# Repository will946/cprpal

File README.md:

# CPRPal — Real-Time CPR Feedback and Training Device

---

## Table of Contents

- [Project Overview](#project-overview)
- [Repository Structure](#repository-structure)
- [System Architecture](#system-architecture)
- [Hardware Components](#hardware-components)
- [Wiring and Pin Assignments](#wiring-and-pin-assignments)
- [PCB Design](#pcb-design)
- [Firmware](#firmware)
- [Operating Modes](#operating-modes)
- [User Operation](#user-operation)
- [Signal Processing](#signal-processing)
- [Power System](#power-system)
- [Cloud and Web Application](#cloud-and-web-application)
- [Setup and Installation](#setup-and-installation)
- [Library Dependencies](#library-dependencies)

---

## Project Overview

CPRPal is a portable, puck-shaped CPR coaching device designed to help untrained bystanders and CPR trainees perform chest compressions with correct force, rhythm, and body positioning during a cardiac emergency or training session.

Sudden cardiac arrest is responsible for approximately 93% of out-of-hospital cardiac arrest deaths. Survival probability drops roughly 10% per minute without CPR or AED intervention, yet only about 3% of the U.S. population is CPR certified annually. CPRPal addresses this gap by providing real-time, easy-to-interpret feedback that requires no prior training to use.

The device is placed between the rescuer's hands and the patient's sternum during chest compressions. It measures compression force directly using a load cell, tracks body posture using a 9-DOF IMU, monitors for heartbeat presence using a PPG optical sensor, and delivers feedback through a color-coded NeoPixel LED ring, a 2.8" TFT LCD display, and a 100 BPM audio metronome buzzer.

**Emergency Mode** operates fully standalone with no Wi-Fi required, providing immediate real-time feedback the moment the button is pressed.

**Training Mode** connects to Wi-Fi, runs a 2-minute guided session, and uploads averaged session metrics to an Azure-hosted cloud dashboard for review.

The final prototype measures 4.5" x 4.5" x 2.25" and runs for over 15 hours on four AA batteries at a normal operating draw of approximately 155 mA.

CPRPal Demo: https://drive.google.com/file/d/1d1auYhc-_jhG4WK9BlywpUfyi4_rIxLO/view?usp=sharing
(Note video isn't perfectly sync with operation)

| Rendering | Final Build |
|---|---|
|  |  | 

---

## Repository Structure

```
CPRPal/
├── 3DModel/
│   └── Mechanical enclosure and CAD files
│       - Top shell with lattice structure and LCD/button/LED cutouts
│       - Bottom shell with battery pocket, support beams, and hard stops
│       - Full assembly files for PLA 3D printing
│
├── ArduinoCode/
│   └── CPRPal.ino — Main ESP32 firmware (FreeRTOS-based)
│       - Sensor integration (HX711, BNO055, PPG)
│       - Real-time signal processing and CPM detection
│       - LED and display feedback systems
│       - Emergency and Training mode logic
│       - Power management and idle sleep
│       - HTTP cloud upload for training sessions
│
├── ArduinoWebsite/
│   └── Azure Static Web App source code
│       - Frontend dashboard (HTML/CSS/JS)
│       - Azure Function API endpoint
│       - Receives HTTP POST from ESP32
│       - Displays training session summary
│
├── PartsList/
│   └── Bill of Materials (BOM) and component references
│
└── PCBFiles/
    └── Full circuit schematics and PCB layout files
        - CPRPal_PCB_Sch — complete schematic
        - Panelized 6-board layout for JLCPCB fabrication
        - Custom PCB footprints and 3D component models
```

---

## System Architecture

CPRPal uses a dual-core FreeRTOS architecture on the Arduino Nano ESP32-S3.

### Core 0 — Sensor Acquisition and Processing

All time-critical sensor tasks run on Core 0 to prevent display rendering overhead from introducing jitter into sensor sampling.

| Task | Function | Sample Rate |
|---|---|---|
| `taskHX711` | Load cell reading, EMA filtering, CPM detection, idle detection | ~80 Hz |
| `taskIMU` | BNO055 orientation reading, tilt computation, posture status | ~40 Hz |
| `taskPPG` | PPG sampling, adaptive peak detection, BPM estimation | ~50 Hz |
| `taskBuzzer` | 100 BPM metronome via LEDC PWM, rhythm LED strip sync | 100 BPM |

### Core 1 — User Interface and Control

The Arduino `loop()` function runs on Core 1 and handles all output rendering:

- TFT display refresh at 10 Hz
- NeoPixel force bar graph refresh at 40 Hz
- Mode selection and session control logic
- Training session timer and metric accumulation
- Serial calibration commands

### Shared State and Synchronization

All shared sensor variables use the `g_` prefix, are declared `volatile`, and are protected by the FreeRTOS mutex `xDataMutex`. A second mutex `xWireMutex` serializes I2C bus access between `taskIMU` and any other bus user. This two-mutex architecture prevents data races while minimizing lock hold time.

---

## Hardware Components

| Component | Part | Purpose |
|---|---|---|
| Microcontroller | Arduino Nano ESP32-S3 | Main processing, Wi-Fi, dual-core FreeRTOS |
| Force Sensor | Half-bridge strain gauge load cell (120 lb) | Direct compression force measurement |
| Load Cell Amplifier | HX711 24-bit ADC | Amplifies and digitizes load cell signal at 80 SPS |
| IMU | Adafruit BNO055 9-DOF Fusion Breakout | Orientation, tilt detection, motion artifact rejection |
| Pulse Sensor | Pulse Sensor Amped (PPG) | Supplemental heartbeat detection |
| Display | Adafruit 2.8" ILI9341 TFT LCD | Real-time prompts and numeric status |
| LED Strips | Adafruit NeoPixel WS2812B (18 total) | Force bar (15 px) and rhythm metronome (3 px) |
| Buzzer | Piezo buzzer | 100 BPM audio metronome |
| Power Regulation | TPS63070 buck-boost converter x2 | Regulated 3.3V and 5V rails from 4xAA batteries |
| Reverse Protection | LM66200 ideal diode x2 | Prevents USB-to-battery reverse current |
| Storage | SanDisk 32GB microSD | Boot animation BMP frames |
| Battery | 4xAA alkaline | 10+ hours runtime at normal operating load |
| Enclosure | PLA 3D print | 4.7" x 4.7" x 2.4" puck housing |

---

## Wiring and Pin Assignments

### ESP32 GPIO Map

| Pin | Peripheral | Function |
|---|---|---|
| GPIO2 | HX711 CLK | Load cell clock |
| GPIO3 | HX711 DOUT | Load cell data |
| GPIO4 | SD Card CS | microSD chip select |
| GPIO6 (D6) | Start Button | Mode selection (active low, internal pull-up) |
| GPIO9 | ILI9341 DC | TFT data/command select |
| GPIO10 | ILI9341 CS | TFT chip select |
| GPIO19 | Buzzer | LEDC PWM channel 0, 2 kHz |
| GPIO21 | PPG LED indicator | Heartbeat flash LED |
| GPIO23 | PPG Sensor | Analog ADC input |
| GPIO2 (LED_PIN) | NeoPixel force bar | 15-pixel WS2812B data |
| GPIO4 (RHYTHM) | NeoPixel rhythm strip | 3-pixel WS2812B data |
| A4 (SDA) | BNO055 SDA | I2C data, 400 kHz |
| A5 (SCL) | BNO055 SCL | I2C clock, 400 kHz |

### I2C Bus

- BNO055 IMU address 0x28
- 10 kOhm pull-up resistors on SDA and SCL
- Bus speed 400 kHz (fast mode)
- External 32.768 kHz crystal for improved BNO055 sensor fusion accuracy

### SPI Bus

- ILI9341 TFT LCD: DC on GPIO9, CS on GPIO10
- microSD: CS on GPIO4
- Both share the hardware SPI bus

### Load Cell Wiring (Half-Bridge)

| Wire Color | HX711 Pin | Function |
|---|---|---|
| RED | E+ | Excitation positive |
| BLACK | E- | Excitation negative |
| WHITE | A- | Signal negative (differential) |
| GREEN | A+ | Signal positive (differential) |
| YELLOW | GND | Common ground reference |

Two 1 kOhm resistors on the HX711 board complete the Wheatstone bridge by providing the two fixed-impedance legs of the half-bridge configuration.

---

## PCB Design

CPRPal uses a custom panelized PCB fabricated by JLCPCB, separated into six press-fit sub-boards using mouse-bite breakaway tabs. Each sub-board can be removed and replaced independently without additional soldering.

### Sub-Board Summary

| Board | Key Components | Output |
|---|---|---|
| 3.3V BuckBoost | TPS63070, LM66200, 213k/365k feedback divider, decoupling caps, 1.5uH inductor | Regulated 3.3V rail |
| 5V BuckBoost | TPS63070, LM66200, alternate feedback divider, decoupling caps, 1.5uH inductor | Regulated 5V rail |
| Power Hub | Distribution headers, 10uF X5R decoupling caps x2 | Common power and ground plane |
| HX711 | HX711 IC, 1kOhm bridge resistors, DOUT/CLK headers | Load cell ADC interface |
| BNO055 IMU | BNO055 breakout, 10kOhm I2C pull-ups, 32.768kHz crystal | Euler angle outputs via I2C |
| ESP32 | Nano ESP32-S3 socket, USB passthrough | Main MCU |
| Bit Shift | Logic level shifter | 3.3V to 5V NeoPixel data translation |

### Component Footprints

#### 3.3V and 5V BuckBoost Boards
| Reference | Component | Footprint |
|---|---|---|
| U1 | TPS63070 — Buck-boost converter | SOT-23-8 |
| U2 | LM66200 — Ideal diode controller | SOT-23-6 |
| L1 | 1.5 µH inductor | Inductor_SMD 4x4mm |
| R1, R2 | Feedback divider resistors (213k / 365k for 3.3V; alternate values for 5V) | 0402 |
| R3 | Current sense resistor | 0402 |
| R4, R6, R7 | Bias/compensation resistors | 0402 |
| C1–C6 | Decoupling and compensation capacitors | 0402 |
| C7 | Output bulk capacitor | 0805 |
| D1 | Schottky diode | SOD-123 |
| J1, J2, J3, J4 | Power input/output headers | PinHeader 1x02 2.54mm |

#### Power Hub Board
| Reference | Component | Footprint |
|---|---|---|
| C10, C11 | 10 µF X5R decoupling capacitors | 0805 |
| J (3.3V) | 3.3V distribution header | PinHeader 2x05 2.54mm |
| J (5V) | 5V distribution header | PinHeader 2x05 2.54mm |
| J (GND) | Ground distribution header | PinHeader 1x08 2.54mm |

#### HX711 Board
| Reference | Component | Footprint |
|---|---|---|
| U1 | HX711 — 24-bit ADC | SOP-16 |
| R5, R8 | 1 kΩ Wheatstone bridge completion resistors | 0402 |
| J (VDD, VCC, DAT, CLK, GND) | MCU interface header | PinHeader 1x05 2.54mm |
| J (RED, BLK, WHT, GRN, YLW) | Load cell wire header | PinHeader 1x05 2.54mm |

#### BNO055 IMU Board
| Reference | Component | Footprint |
|---|---|---|
| U1 | BNO055 — 9-DOF IMU | LGA-28 (custom) |
| X1 | 32.768 kHz crystal | Crystal SMD 3.2x1.5mm |
| R1, R2 | 10 kΩ I2C pull-up resistors | 0402 |
| J7 | Configuration header (PS0, PS1, ADR, INT) | PinHeader 1x04 2.54mm |
| J (RST, SDA, SCL, GND, 3V, VIN) | MCU interface header | PinHeader 1x06 2.54mm |

#### ESP32 Board
| Reference | Component | Footprint |
|---|---|---|
| U1 | Arduino Nano ESP32-S3 | Custom dual-row female socket, 2x15 2.54mm |
| J (USB) | USB-C passthrough cutout | USB-C receptacle footprint |
| J (left, right) | GPIO breakout headers | PinHeader 1x15 2.54mm x2 |

#### Bit Shift Board
| Reference | Component | Footprint |
|---|---|---|
| U3 | 74AHCT125 — Quad level shifter | SOIC-14 |
| R10 | Pull-down resistor | 0402 |
| J (input) | 3.3V NeoPixel data input header | PinHeader 1x02 2.54mm |
| J (output) | 5V NeoPixel data output header | PinHeader 1x02 2.54mm |
| J (VCC, GND) | Power headers | PinHeader 1x02 2.54mm |

### Power Architecture

Two independent TPS63070 buck-boost converters are used instead of a single converter with an LDO post-regulator. This improves efficiency across the full 4xAA discharge range (approximately 6V fully charged to 4.8V near end of life), since the buck-boost topology maintains tight output regulation without the linear losses an LDO would introduce at shrinking headroom.

- 3.3V rail powers: ESP32-S3, BNO055 IMU, PPG sensor, piezo buzzer
- 5V rail powers: ILI9341 LCD, NeoPixel strips (18 px total), HX711 amplifier

---

## Firmware

The firmware is a single Arduino sketch located in `ArduinoCode/CPRPal.ino`. It is written in C++ using the Arduino framework for ESP32 and relies on FreeRTOS task management, mutex-protected shared state, and the ESP32's LEDC hardware PWM peripheral for the buzzer metronome.

### Key Constants

```cpp
// Force feedback thresholds (lbs)
const float FORCE_THRESHOLD_LB      = 30.0f;   // Rising edge detection
const float FORCE_LOW_OK            = 75.0f;   // Below = TOO LIGHT (yellow)
const float FORCE_HIGH_OK           = 110.0f;  // Above = TOO STRONG (red)

// CPM thresholds
const float CPM_LOW_OK              = 100.0f;  // Below = TOO SLOW
const float CPM_HIGH_OK             = 120.0f;  // Above = TOO FAST
const unsigned long CPM_DEBOUNCE_MS = 180UL;   // Anti-bounce window
const int CPM_INTERVAL_COUNT        = 6;       // Rolling average window size

// Tilt feedback
const float TILT_WARN_DEG           = 8.0f;    // Above = ADJUST

// Timing
const unsigned long IDLE_TIMEOUT_MS     = 20000UL;  // 20s inactivity -> idle
const unsigned long TRAINING_SESSION_MS = 120000UL; // 2-minute session
const unsigned long TRAINING_SAMPLE_MS  = 3000UL;   // Sample every 3s
const unsigned long TRAINING_HOLD_MS    = 3000UL;   // Button hold -> Training

// Buzzer metronome
#define BUZZER_FREQ_HZ    2000  // 2 kHz tone
#define BUZZER_BEEP_MS    30    // On-time per beat in ms
#define BUZZER_PERIOD_MS  600   // Full period = 100 BPM

// Load cell
float calibration_factor = 6500; // Raw counts per pound-force (empirical)
```

### Live Serial Calibration Commands

The calibration factor can be adjusted without reflashing firmware using the Serial Monitor at 115200 baud:

| Key | Action |
|---|---|
| `+` or `a` | Increase calibration factor by 10 |
| `-` or `z` | Decrease calibration factor by 10 |
| `t` or `T` | Tare the scale (zero current load) |
| `r` or `R` | Reset session peak weight |

### EMA Filter

Raw load cell readings are smoothed before any threshold detection:

```
w_filtered[n] = 0.75 * w_filtered[n-1] + 0.25 * w_raw[n]
```

Smoothing factor alpha = 0.25 was chosen empirically to balance noise rejection against compression onset detection latency.

### CPM Detection Algorithm

1. EMA-filtered force crosses above FORCE_THRESHOLD_LB (30 lb) — rising edge detected
2. 180ms debounce window prevents double-counting from signal ringing near threshold
3. Inter-edge interval converted to instantaneous CPM: `CPM = 60000 / delta_t_ms`
4. Stored in 6-entry circular buffer; rolling CPM = arithmetic mean of buffer entries
5. If no compression detected for 2000ms, CPM resets to zero and buffer clears

### IMU Baseline Calibration

On startup, 100 BNO055 orientation samples are captured (after 50 warm-up discards) and averaged as the resting baseline. All subsequent readings are deltas from this baseline so tilt feedback is relative to device placement on the patient, not absolute gravity direction.

- Tilt magnitude = sqrt(delta_roll² + delta_pitch²)
- Above 5 degrees triggers ADJUST on LCD
- Above 10 degrees triggers LEAN on LCD

### PPG Detection Algorithm

1. ADC sampled at ~50 Hz, 12-bit resolution, 3.6V full-scale attenuation
2. 10-sample moving average applied for noise reduction
3. Adaptive baseline tracks slow DC component of signal
4. Adaptive peak envelope tracks signal upper bound
5. Beat detected on rising edge exceeding 55% of amplitude above baseline
6. Flag resets when signal falls below 35% of amplitude (hysteresis)
7. BPM = average of 4 most recent valid inter-beat intervals
8. BPM zeroed after 3.5s without a detected beat
9. Finger contact confirmed when ADC reading exceeds FINGER_ON threshold (1700)

---

## Operating Modes

### Boot Sequence

On power-on the device performs the following sequence automatically:

1. Serial initialization and reset reason diagnostic printout to serial monitor
2. I2C bus initialization at 400 kHz on pins A4 and A5
3. BNO055 initialization and external crystal enable
4. SPI bus and TFT display initialization
5. Boot animation — 8 BMP frames loaded sequentially from microSD, 1.25s per frame
6. NeoPixel strip initialization at 40/255 brightness
7. HX711 initialization, power-up, and tare to zero
8. FreeRTOS sensor tasks spawned on Core 0
9. Mode selection screen displayed
10. User selects mode via button
11. IMU orientation baseline captured in current resting position

### Emergency Mode

Activated by a short press of the start button.

- Wi-Fi fully disabled — no radio activity during emergency
- 100 BPM metronome starts immediately
- Live CPM, force, tilt, and PPG status shown on TFT display
- NeoPixel force bar updates at 40 Hz
- After 20s of inactivity (no load cell change exceeding 10 lb), all sensor tasks are suspended in RAM and device enters software idle mode at approximately 95 mA
- To wake: hold button for 2 seconds; all peripherals reinitialize and device returns to mode selection

### Training Mode

Activated by holding the button for 3 seconds.

- Wi-Fi connection attempted with 10s timeout
- If no network found: graceful offline fallback, session runs locally, no upload at end
- 2-minute timed session with countdown timer displayed on LCD bottom-right
- Sensor metrics sampled every 3s into running sum accumulators
- At session end: averages computed, JSON serialized manually, HTTP POST sent to Azure endpoint
- Session summary displayed on LCD regardless of upload success
- Wi-Fi fully shut down after upload; device returns to mode selection

---

## User Operation

### Emergency Mode Step-by-Step

1. Remove CPRPal from first aid kit and slide power switch on. Keep device still on a flat surface during the ~5 second boot and IMU calibration sequence.
2. Call 911 immediately or direct a bystander to call. Do not delay emergency services.
3. Place CPRPal face-up on the center of the patient's chest, between the nipple line, with the LCD visible to you.
4. Short-press the start button once. Emergency Mode begins and the metronome starts at 100 BPM.
5. Place both hands on top of the device and compress in time with the beep and amber LED ring.
6. Watch the side LED bar: yellow = push harder, green = good depth, red = ease up.
7. Watch LCD TILT row: ADJUST or LEAN means recheck your body position and ensure force is going straight down.
8. Watch LCD PPG row: Heartbeat detect means consider pausing to reassess for pulse.
9. Continue compressions until EMS arrives or AED is ready.

### Training Mode Step-by-Step

1. Power on and hold button for 3 seconds until "Training selected" appears on LCD.
2. Device connects to Wi-Fi and displays IP address on successful connection.
3. Scan QR code on device or navigate to the dashboard URL on a phone or computer.
4. Begin compressions following the same LED and LCD feedback as Emergency Mode.
5. 2-minute countdown timer shown at bottom right of LCD throughout session.
6. At session end, summary shown on LCD and data uploaded to dashboard if Wi-Fi available.

### Feedback Reference

| Channel | States | Meaning |
|---|---|---|
| LCD — CPM | WAITING / TOO SLOW / GOOD / TOO FAST | Compression rate guidance toward 100-120 CPM |
| LCD — Force | TOO LIGHT / GOOD / TOO STRONG | Compression depth guidance toward AHA target |
| LCD — Tilt | GOOD / ADJUST / LEAN | Posture and off-axis warning |
| LCD — PPG | BPM value / Heartbeat detect / Missing heartbeat | Supplemental pulse status |
| NeoPixel bar | Yellow / Green / Red | Visual force classification |
| Buzzer + rhythm LEDs | 100 BPM beep + amber flash | Compression pacing metronome |

---

## Signal Processing

### Force Classification

| Force Range | LED Color | LCD Status | Meaning |
|---|---|---|---|
| < 5 lb | Off | — | No significant contact |
| 5–75 lb | Yellow | TOO LIGHT | Insufficient compression force |
| 75–110 lb | Green | GOOD | Target depth range |
| > 110 lb | Red | TOO STRONG | Excessive force |

### CPM Classification

| CPM Range | LCD Status |
|---|---|
| < 1 | WAITING |
| 1–99 | TOO SLOW |
| 100–120 | GOOD |
| > 120 | TOO FAST |

### Tilt Classification

| Tilt Magnitude | LCD Status |
|---|---|
| < 5 degrees | GOOD |
| 5–10 degrees | ADJUST |
| > 10 degrees | LEAN |

---

## Power System

### Rail Assignments

| Rail | Powered Components |
|---|---|
| 3.3V | ESP32-S3, BNO055 IMU, PPG sensor, piezo buzzer |
| 5V | ILI9341 LCD, NeoPixel strips (18 px total), HX711 amplifier |

### Power Budget

| Operating Mode | Current Draw | Notes |
|---|---|---|
| Peak startup | ~235 mA | Boot animation with full brightness LEDs and LCD |
| Normal (Emergency Mode) | ~155 mA | Colored LEDs at 40/255, dim LCD, all sensors active |
| Idle (tasks suspended) | ~95 mA | LCD dim showing idle screen, ESP32 running, all else off |
| Training Mode | ~195 mA | Normal + 40 mA Wi-Fi radio, no idle mode |

At 155 mA normal draw with a 2700 mAh 4xAA pack, theoretical runtime is approximately 17 hours. Measured battery life exceeded 10 hours under mixed-use testing.

---

## Cloud and Web Application

### Dashboard URL

```
https://gentle-stone-0c20e761e.6.azurestaticapps.net/
```

The dashboard is a static web application hosted on Microsoft Azure Static Web Apps using the free tier only. No charges are incurred.

### Data Flow

```
ESP32 collects sensor data every 3s during Training Mode session
  -> Averages computed at 2-minute session end
  -> JSON payload manually serialized (no external library)
  -> HTTP POST to Azure Function API endpoint
  -> Azure processes and stores payload
  -> Dashboard displays session summary
```

### JSON Payload Format

```json
{
  "deviceId": "nano-esp32-test",
  "timestamp": "123456789",
  "mode": "TRAINING",
  "sessionType": "summary",
  "ppg": 1800,
  "imuY": 2.5,
  "imuZ": -1.2,
  "compressionRate": 110,
  "compressionDepth": 85.3,
  "recoil": 1,
  "status": "Good compressions",
  "sampleCount": 40,
  "sessionDurationMs": 120000
}
```

### Status String Logic

| Condition | Status Field Value |
|---|---|
| Rate > 125 CPM or depth > 6.2 lb | `"Bad: too fast/deep"` |
| Rate < 100 CPM or depth < 5.0 lb or recoil == 0 | `"Warn: shallow/recoil"` |
| All within range | `"Good compressions"` |

### Offline Fallback

If Wi-Fi is unavailable when Training Mode is entered:

1. Device displays offline warning on LCD
2. Full 2-minute session runs locally with all normal feedback active
3. Session summary displayed on LCD at session end
4. HTTP POST upload skipped

---

## Setup and Installation

### Requirements

- Arduino IDE 2.x
- Arduino ESP32 board package installed via Boards Manager
  - Search for `esp32` by Espressif Systems
  - Select board: **Arduino Nano ESP32**

### Step 1 — Install Required Libraries

Open Arduino IDE and go to Sketch -> Include Library -> Manage Libraries. Search for and install each of the following:

| Library | Author |
|---|---|
| Adafruit BNO055 | Adafruit |
| Adafruit BusIO | Adafruit |
| Adafruit EPD | Adafruit |
| Adafruit FT6206 Library | Adafruit |
| Adafruit GFX Library | Adafruit |
| Adafruit HX8357 Library | Adafruit |
| Adafruit ILI9341 | Adafruit |
| Adafruit ImageReader Library | Adafruit |
| Adafruit NeoMatrix | Adafruit |
| Adafruit NeoPixel | Adafruit |
| Adafruit seesaw Library | Adafruit |
| Adafruit SH110X | Adafruit |
| Adafruit SPIFlash | Adafruit |
| Adafruit SSD1331 OLED Driver Library for Arduino | Adafruit |
| Adafruit SSD1351 library | Adafruit |
| Adafruit ST7735 and ST7789 Library | Adafruit |
| Adafruit STMPE610 | Adafruit |
| Adafruit TouchScreen | Adafruit |
| Adafruit TSC2007 | Adafruit |
| Adafruit Unified Sensor | Adafruit |
| HX711 | bogde |
| PulseSensor Playground | World Famous Electronics |
| SdFat - Adafruit Fork | Adafruit |

> WiFi and HTTPClient are included with the ESP32 Arduino core and do not require separate installation.

### Step 2 — Prepare the microSD Card

The boot animation requires 8 BMP image files placed in the root of a FAT32-formatted microSD card. Name the files exactly as follows:

```
/Step0.bmp
/Step1.bmp
/Step2.bmp
/Step3.bmp
/Step4.bmp
/Step5.bmp
/Step6.bmp
/Step7.bmp
```

Each image should be a 24-bit BMP at 240x320 pixels to match the ILI9341 display resolution. If the SD card fails to mount, the firmware will halt and display an error on the TFT screen.

### Step 3 — Configure Wi-Fi Credentials

Open `ArduinoCode/CPRPal.ino` and locate the following lines near the top of the file:

```cpp
const char* WIFI_SSID     = "YOUR_SSID_HERE";
const char* WIFI_PASSWORD = "YOUR_PASSWORD_HERE";
```

Replace with your Wi-Fi network credentials. Wi-Fi is only used during Training Mode. Emergency Mode runs fully offline regardless of these settings.

> Note: The ESP32 posts directly to the Azure cloud endpoint over any internet-connected Wi-Fi network. The viewing device does not need to be on the same network as the ESP32.

### Step 4 — Select Board and Port

In Arduino IDE:

1. Go to Tools -> Board -> esp32 -> Arduino Nano ESP32
2. Go to Tools -> Port -> select the correct COM port for your device
3. If the board is not recognized, hold the BOOT button on the ESP32 while connecting USB

### Step 5 — Flash Firmware

Click Upload in Arduino IDE. Open the Serial Monitor at 115200 baud to view boot diagnostics, reset reason history, sensor readings, and calibration output.

### Step 6 — Calibrate the Load Cell

1. Power on the device and let it boot fully
2. Open Serial Monitor at 115200 baud
3. Place a known weight on the device
4. Use `+` and `-` keys in Serial Monitor to adjust calibration factor until the displayed value matches the known weight
5. Note the final calibration factor and update `calibration_factor` in the sketch to save it permanently

---

## Library Dependencies

| Library | Purpose in CPRPal |
|---|---|
| Adafruit BNO055 | BNO055 IMU driver and Euler angle output |
| Adafruit BusIO | I2C/SPI abstraction layer required by Adafruit sensor libraries |
| Adafruit GFX Library | Core graphics primitives for TFT display rendering |
| Adafruit ILI9341 | ILI9341 TFT display driver |
| Adafruit ImageReader Library | BMP image loading from SD card for boot animation |
| Adafruit NeoPixel | WS2812B addressable LED control for force bar and rhythm strip |
| Adafruit NeoMatrix | NeoPixel matrix support (dependency) |
| Adafruit Unified Sensor | Unified sensor abstraction required by BNO055 driver |
| Adafruit SPIFlash | SPI flash support (alternative storage backend) |
| SdFat - Adafruit Fork | SD card FAT filesystem for microSD BMP loading |
| Adafruit EPD | E-paper display support (dependency) |
| Adafruit FT6206 Library | Capacitive touchscreen support (dependency) |
| Adafruit HX8357 Library | HX8357 display driver (dependency) |
| Adafruit seesaw Library | Adafruit seesaw breakout support (dependency) |
| Adafruit SH110X | OLED display driver (dependency) |
| Adafruit SSD1331 OLED Driver | SSD1331 OLED support (dependency) |
| Adafruit SSD1351 library | SSD1351 OLED support (dependency) |
| Adafruit ST7735 and ST7789 Library | ST77xx display drivers (dependency) |
| Adafruit STMPE610 | Touch controller support (dependency) |
| Adafruit TouchScreen | Resistive touchscreen support (dependency) |
| Adafruit TSC2007 | Touch controller support (dependency) |
| HX711 by bogde | HX711 load cell amplifier driver |
| PulseSensor Playground | PPG pulse sensor signal processing |

*CPRPal is a prototype device developed for educational purposes. It is not a certified medical device. Always call emergency services first in a cardiac emergency.*

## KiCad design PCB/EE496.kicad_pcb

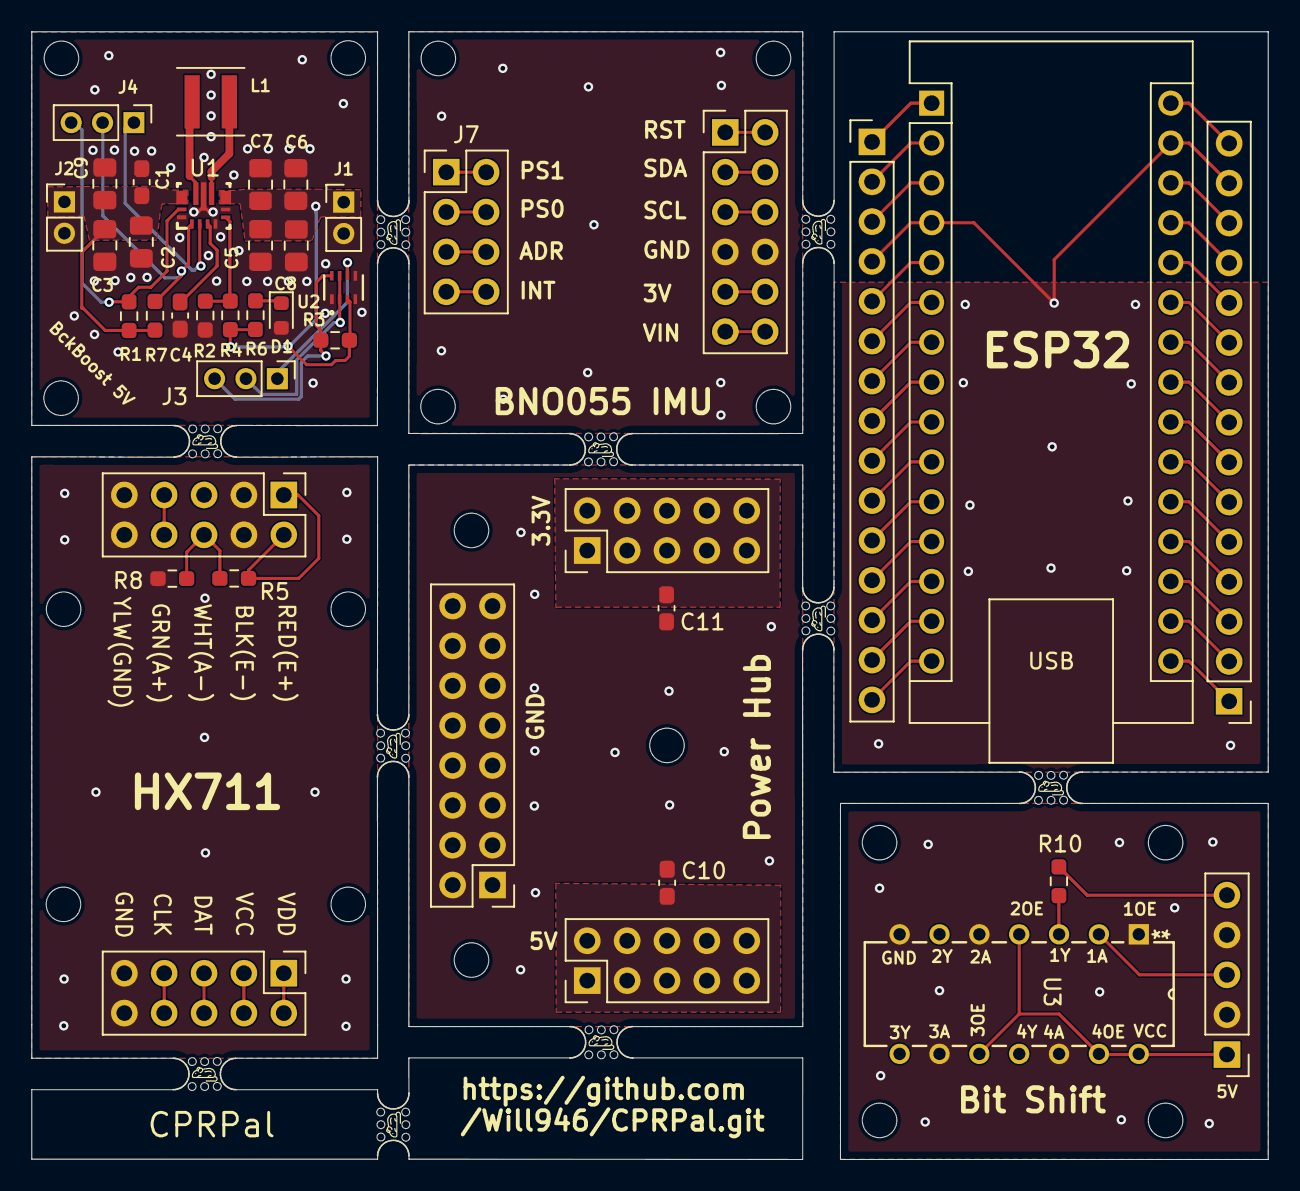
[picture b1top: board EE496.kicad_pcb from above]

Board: 2 copper layers, 78.8 x 71.9 mm, 68 parts (0 on the bottom side), 62 nets.

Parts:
A1: Arduino_Nano_ESP32; Arduino_Nano
C1, C4: 0.1uF; C_0603_1608Metric_Pad1.08x0.95mm_HandSolder
C2, C3, C5, C9: 10uF; C_0805_2012Metric_Pad1.18x1.45mm_HandSolder
C6, C7, C8: 22uF; C_0805_2012Metric_Pad1.18x1.45mm_HandSolder
C10, C11: 100nF; C_0603_1608Metric_Pad1.08x0.95mm_HandSolder
D1: RED; LED_0603_1608Metric
H1, H2, H3, H4, H5, H6, H7, H8, H9, H10, H11, H12, H13, H14, H15, H16, H17, H19: MountingHole; MountingHole_2.2mm_M2
J1, J2: Conn_01x02_Pin; PinHeader_1x02_P2.00mm_Vertical
J3, J4: Conn_01x03_Pin; PinHeader_1x03_P2.00mm_Vertical
J5: Conn_01x05_Pin; PinHeader_1x05_P2.54mm_Vertical
J6, J9, J13, J14: Conn_02x05_Odd_Even; PinHeader_2x05_P2.54mm_Vertical
J7: Conn_02x04_Odd_Even; PinHeader_2x04_P2.54mm_Vertical
J8: Conn_02x06_Odd_Even; PinHeader_2x06_P2.54mm_Vertical
J10, J11: Conn_01x15_Pin; PinHeader_1x15_P2.54mm_Vertical
J12: Conn_02x08_Odd_Even; PinHeader_2x08_P2.54mm_Vertical
L1: 1.5uH; L_Coilcraft_XxL4020
R1, R7: 10k; R_0603_1608Metric_Pad0.98x0.95mm_HandSolder
R2: 68.1k; R_0603_1608Metric_Pad0.98x0.95mm_HandSolder
R3: 50k; R_0603_1608Metric_Pad0.98x0.95mm_HandSolder
R4: 365k; R_0603_1608Metric_Pad0.98x0.95mm_HandSolder
R5, R8: 1K; R_0603_1608Metric_Pad0.98x0.95mm_HandSolder
R6: 1k; R_0603_1608Metric_Pad0.98x0.95mm_HandSolder
R10: 10K; R_0603_1608Metric_Pad0.98x0.95mm_HandSolder
U1: TPS63070; RNM0015A
U2: LM66200DRLR; SOT-5X3_DRL_TEX-L
U3: SN74AHCT125N; N14
mouse-bite-2mm-4mm, mouse-bite-2mm-4mm#2, mouse-bite-2mm-4mm#3, mouse-bite-2mm-4mm#4, mouse-bite-2mm-4mm#5, mouse-bite-2mm-4mm#6, mouse-bite-2mm-4mm#7, mouse-bite-2mm-4mm#8, mouse-bite-2mm-4mm#9, mouse-bite-2mm-4mm#10: VAL**; mouse-bite-2mm-4mm

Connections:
3.3V: C11.2, J14.1, J14.2, J14.3, J14.4, J14.5, J14.6, J14.7, J14.8, J14.9, J14.10
3.3Vi: J5.3, U3.2 (1A)
3V: J8.9, J8.10
3v3: A1.17 (3V3), J10.2
5V: C10.2, J5.1, J13.1, J13.2, J13.3, J13.4, J13.5, J13.6, J13.7, J13.8, J13.9, J13.10, U3.4 (*2OE), U3.10 (*3OE), U3.13 (*4OE), U3.14 (VCC)
5Vout: J3.2, U2.2 (VOUT), U2.7 (VOUT)
/FB: R2.2, R4.1, U1.5 (FB)
/PG: J4.1, U1.2 (PG)
/PS: J4.2, R7.1, U1.1 (PS/SYNC)
/~EN: J4.3, R1.1, U1.14 (~EN)
A0: A1.19 (A0), J10.4
A1: A1.20 (A1), J10.5
A2: A1.21 (A2), J10.6
A3: A1.22 (A3), J10.7
A6: A1.25 (A6), J10.10
A7: A1.26 (A7), J10.11
A+: J9.7, J9.8
A-: J9.6, R5.2, R8.2
ADR: J7.5, J7.6
AVDD: J9.1, J9.2, R5.1
B0: A1.18 (B0), J10.3
B1: A1.28 (B1), J10.13
D1/TX: A1.1 (D1/TX), J11.1
D2: A1.5 (D2), J11.5
D3: A1.6 (D3), J11.6
D4: A1.7 (D4), J11.7
D5: A1.8 (D5), J11.8
D6: A1.9 (D6), J11.9
D7: A1.10 (D7), J11.10
D8: A1.11 (D8), J11.11
D9: A1.12 (D9), J11.12
D10/CS: A1.13 (D10/CS), J11.13
D11/COPI: A1.14 (D11/COPI), J11.14
D12/CIPO: A1.15 (D12/CIPO), J11.15
D13/SCK: A1.16 (D13/SCK), J10.1
DAT: J6.5, J6.6
DO/RX: A1.2 (D0/RX), J11.2
GND: A1.4 (GND), A1.29 (GND), C1.2, C2.2, C3.2, C4.2, C5.2, C6.2, C7.2, C8.2, C9.2, C10.1, C11.1, D1.2 (C), J1.2, J2.2, J5.2, J5.4, J6.9, J6.10, J8.7, J8.8, J9.3, J9.4, J9.9, J9.10, J10.14, J11.4, J12.1, J12.2, J12.3, J12.4, J12.5, J12.6, J12.7, J12.8, J12.9, J12.10, J12.11, J12.12, J12.13, J12.14, J12.15, J12.16, R2.1, R8.1, U1.4 (GND), U1.6 (FB2), U1.10 (PGND), U1.15 (VSEL), U2.1 (GND), U2.4 (ON), U2.5 (GND), U3.1 (*1OE), U3.5 (2A), U3.7 (GND), U3.9 (3A), U3.12 (4A)
INT: J7.7, J7.8
unnamed: D1.1 (A), R6.1
unnamed: L1.1, U1.11 (L1)
unnamed: L1.2, U1.9 (L2)
unnamed: C4.1, U1.3 (VAUX)
unnamed: R10.2, U3.3 (1Y)
Out: J5.5, R10.1
PS0: J7.3, J7.4
PS1: J7.1, J7.2
RESET: A1.3 (~RESET), J11.3
RST: J8.1, J8.2
SCK: J6.7, J6.8
SCL: J8.5, J8.6
SCL/A5: A1.24 (SCL/A5), J10.9
SDA: J8.3, J8.4
SDA/A4: A1.23 (SDA/A4), J10.8
St: J3.3, R3.2, U2.8 (ST)
VCC: J6.3, J6.4
VDD: J6.1, J6.2
VIN: A1.30 (VIN), J8.11, J8.12, J10.15
VUSB/5V: A1.27 (VUSB/5V), J10.12
Vin: C1.1, C2.1, C3.1, C9.1, J2.1, R1.2, R7.2, U1.12 (13), U1.13
Vin2: J3.1, U2.6 (VIN2)
Vout: C5.1, C6.1, C7.1, C8.1, J1.1, R3.1, R4.2, R6.2, U1.7 (8), U1.8, U2.3 (VIN1)

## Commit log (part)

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2026-05-08 Upload
